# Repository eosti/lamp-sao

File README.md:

# Lamp SAOs
A few lamp-related SAOs. 

## HPL Lamp SAO

### Build Notes
- Requires 2x 28mm LED filaments and 2x ??mm 0.8mm dia. "jewelery wire" (tinned copper? not sure)
- Bend the longer wire so that it has a ?-shape on top and a very slight jog to the left (front view) towards the bottom
- Using the smaller jig, solder the non-hole side to the ? shape to form the filament assembly
- Using the larger jig, solder to SAO
- Bend another wire that makes a complicated shape. It's hard to explain in words. Solder this to the SAO. 
- Solder the other end to the bottom of the filaments. MAKE SURE THE TWO WIRES AREN'T BRIDGED. 

### Changelog
**V0 -> V1**
- Flip NPN footprints to be correct
- Reduce R5 to 30ohm
- Thermal relief on GND wire pad
- Replace 2N3904 with dual 3904 package
- Be a bit less hacky with the external PWM buffer
- Replace 555 diodes with a dual diode package

## C9 Lamp SAO
A SAO based on a C9 holiday lamp. 

### Build Notes
- Requires 2x 28mm LED filaments and 1x 28mm 0.8mm dia. "jewelery wire" (tinned copper? not sure)
- Using the C9 jig, solder the two filaments and the wire to the PCB
    - The hole-side of the filament should be on the top of the SAO, and the side of the filament that has a white rectangle peeking through should be on the back side of the SAO
    - For white filaments, the side that looks more orange should be facing the front of the SAO
- Remove from jig, and then solder the tops of the filaments to the wire on the front side
    - May need to bend the wire forward a bit to be coplanar with the filament leads
- Trim top of wire

### Changelog
- Schematics the same as HPL v1

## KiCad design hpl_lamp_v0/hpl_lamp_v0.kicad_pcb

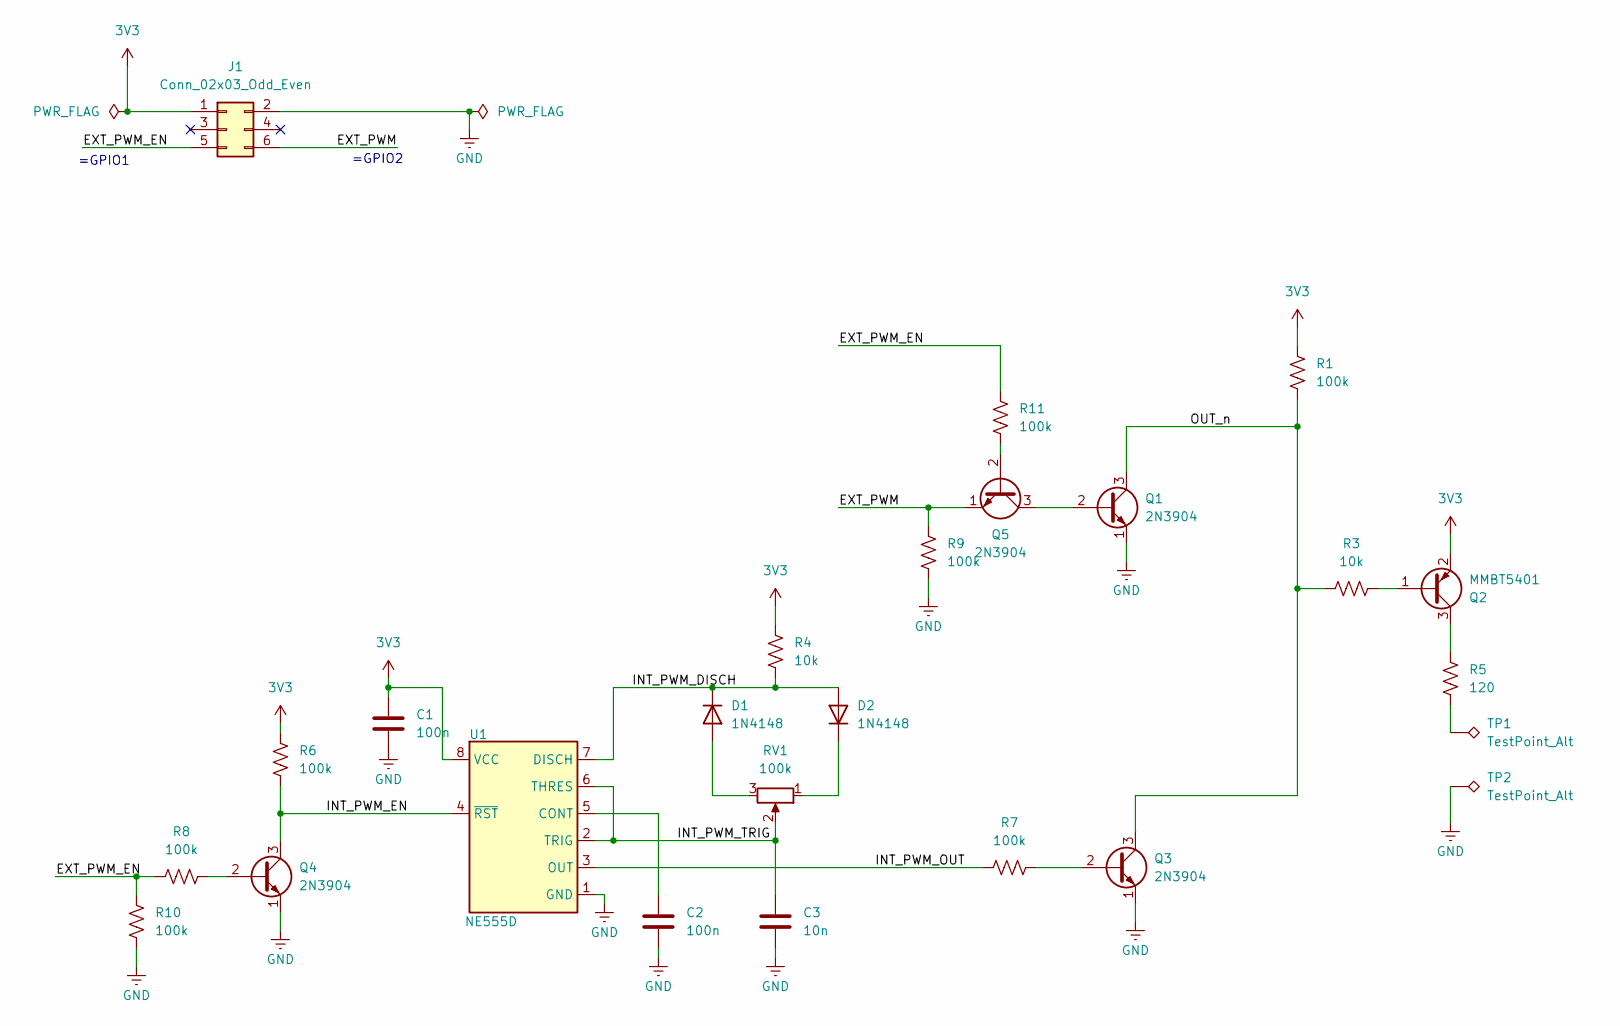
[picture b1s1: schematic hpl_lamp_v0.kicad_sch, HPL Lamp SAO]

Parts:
C1, C2: 100n; C_0603_1608Metric; LCSC C14663
C3: 10n; C_0603_1608Metric; LCSC C57112
D1, D2: 1N4148; D_SOD-323; LCSC C2128
J1: Conn_02x03_Odd_Even; IDC-Header_2x03_P2.54mm_Vertical
Q1, Q3, Q4, Q5: 2N3904; SOT-23; LCSC C20526
Q2: MMBT5401; SOT-23; LCSC C8326
R1, R6, R7, R8, R9, R10, R11: 100k; R_0603_1608Metric; LCSC C25803
R3, R4: 10k; R_0603_1608Metric; LCSC C25804
R5: 120; R_0805_2012Metric; LCSC C17437
RV1: 100k; Potentiometer_Bourns_TC33X_Vertical; LCSC C48997895
TP1, TP2: TestPoint_Alt; filament_connection
U1: NE555D; SOIC-8_3.9x4.9mm_P1.27mm; LCSC C7593

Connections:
3V3: C1.1, J1.1, Q2.2 (E), R1.1, R4.1, R6.1, U1.8 (VCC)
/EXT_PWM: J1.6, Q5.1 (E), R9.1; also elsewhere on the board
/EXT_PWM_EN: J1.5, R8.2, R10.1, R11.1
/INT_PWM_DISCH: D1.1 (K), D2.2 (A), R4.2, U1.7 (DISCH)
/INT_PWM_EN: Q4.3 (C), R6.2, U1.4 (~RST)
/INT_PWM_OUT: R7.2, U1.3 (OUT)
/INT_PWM_TRIG: C3.1, RV1.2, U1.2 (TRIG), U1.6 (THRES)
/OUT_n: Q1.3 (C), Q3.3 (C), R1.2, R3.2
GND: C1.2, C2.2, C3.2, J1.2, Q1.1 (E), Q3.1 (E), Q4.1 (E), R9.2, R10.2, TP2.1 (1_1), U1.1 (GND)
unnamed: D1.2 (A), RV1.3
unnamed: D2.1 (K), RV1.1
unnamed 11: Q1.2 (B), Q5.3 (C); also elsewhere on the board
unnamed: Q2.1 (B), R3.1
unnamed: Q2.3 (C), R5.1
unnamed: Q3.2 (B), R7.1
unnamed: Q4.2 (B), R8.1
unnamed: Q5.2 (B), R11.2
unnamed: R5.2, TP1.1 (1_1)
unnamed: C2.1, U1.5 (CONT)

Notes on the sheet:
=GPIO2
=GPIO1

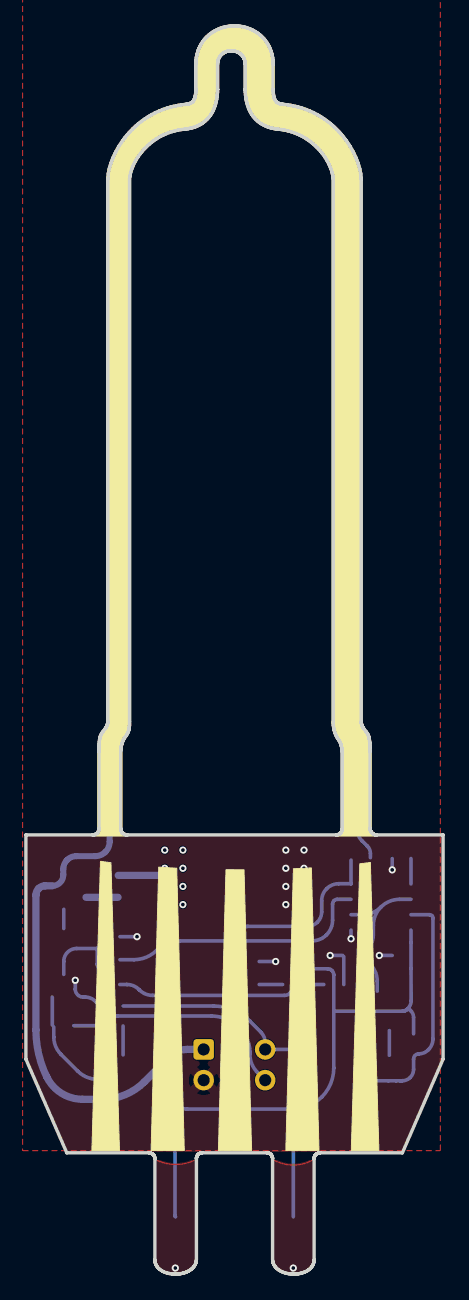
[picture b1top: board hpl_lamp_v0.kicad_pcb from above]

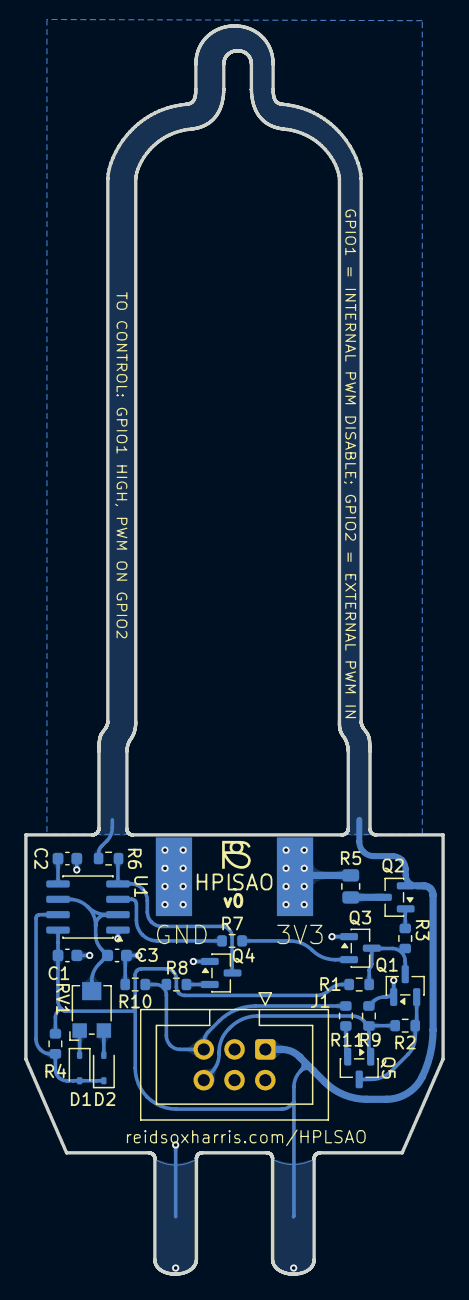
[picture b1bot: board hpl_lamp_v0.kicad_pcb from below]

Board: 2 copper layers, 34.5 x 103.1 mm, 26 parts (26 on the bottom side), 19 nets.

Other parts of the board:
R2: 10k; R_0603_1608Metric

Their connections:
/EXT_PWM: R2.2; also elsewhere on the board
unnamed 11: R2.1; also elsewhere on the board

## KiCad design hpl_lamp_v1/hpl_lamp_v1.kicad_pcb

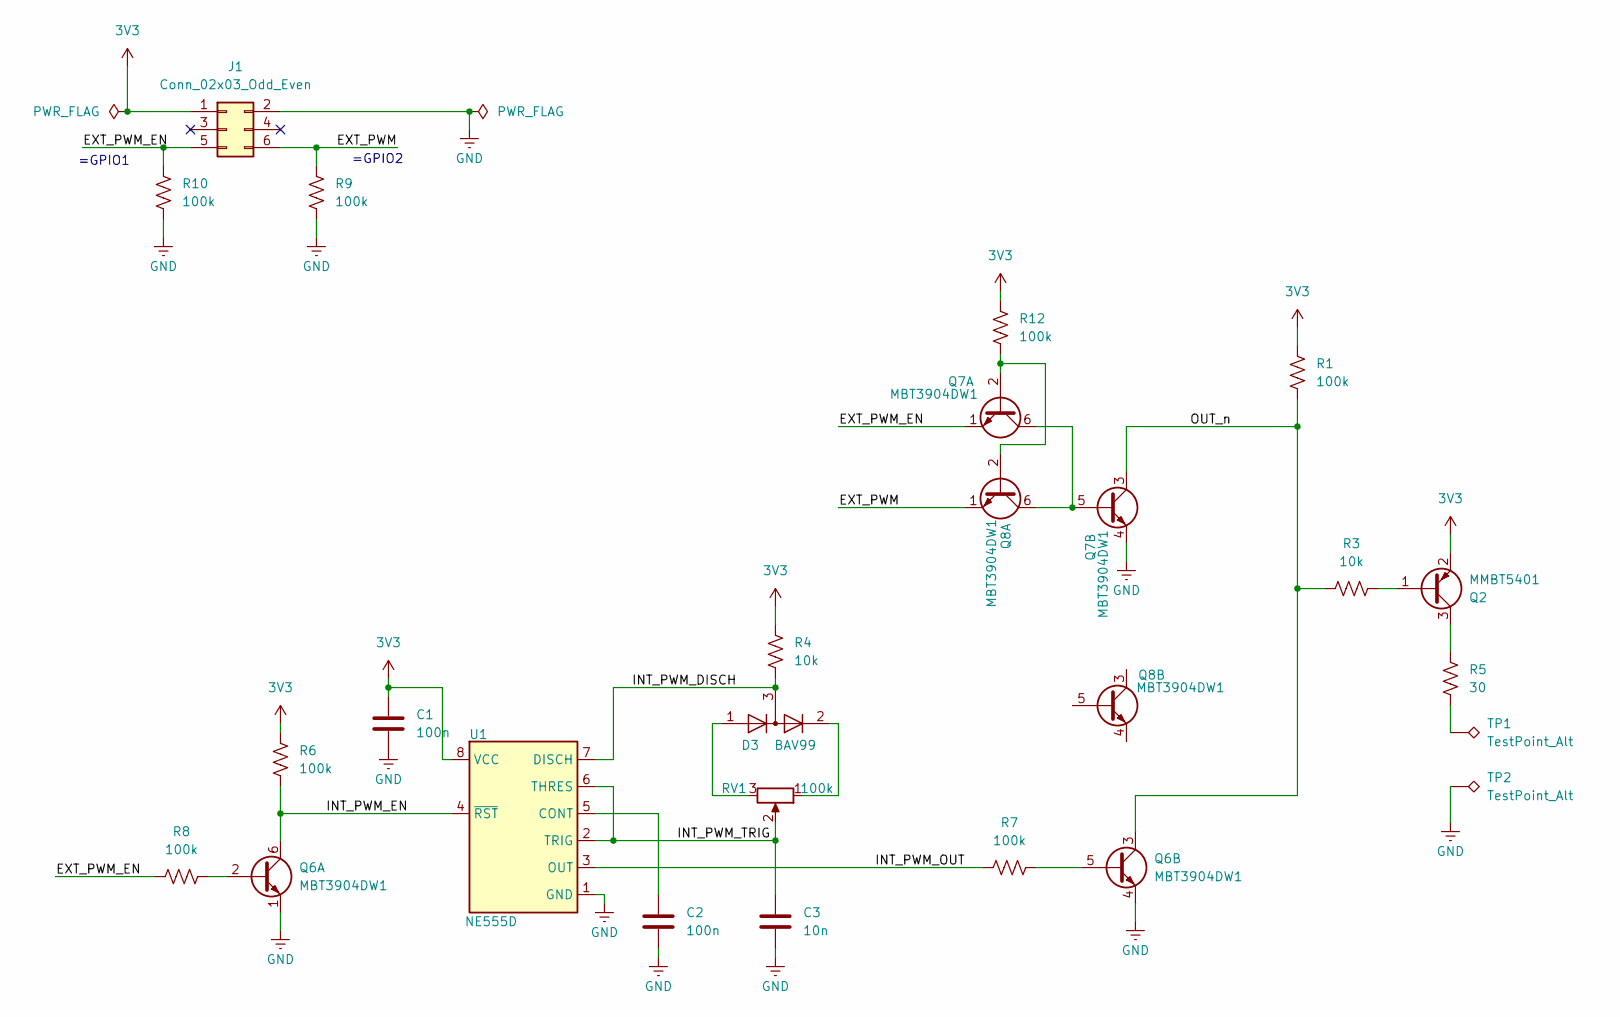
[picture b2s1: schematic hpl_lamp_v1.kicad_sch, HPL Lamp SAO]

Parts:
C1, C2: 100n; C_0603_1608Metric; LCSC C14663
C3: 10n; C_0603_1608Metric; LCSC C57112
D3: BAV99; SOT-23
J1: Conn_02x03_Odd_Even; PinHeader_2x03_P2.54mm_Vertical_SMD
Q2: MMBT5401; SOT-23; LCSC C8326
Q6, Q7, Q8: MBT3904DW1; SOT-363_SC-70-6
R1, R6, R7, R8, R9, R10, R12: 100k; R_0603_1608Metric; LCSC C25803
R3, R4: 10k; R_0603_1608Metric; LCSC C25804
R5: 30; R_0805_2012Metric; LCSC C17437
RV1: 100k; Potentiometer_Bourns_TC33X_Vertical; LCSC C48997895
TP1, TP2: TestPoint_Alt; filament_connection
U1: NE555D; SOIC-8_3.9x4.9mm_P1.27mm; LCSC C7593

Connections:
3V3: C1.1, J1.1, Q2.2 (E), R1.1, R4.1, R6.1, R12.1, U1.8 (VCC)
/EXT_PWM: J1.6, Q8.1 (E1), R9.1
/EXT_PWM_EN: J1.5, Q7.1 (E1), R8.2, R10.1
/INT_PWM_DISCH: D3.3 (K), R4.2, U1.7 (DISCH)
/INT_PWM_EN: Q6.6 (C1), R6.2, U1.4 (~RST)
/INT_PWM_OUT: R7.2, U1.3 (OUT)
/INT_PWM_TRIG: C3.1, RV1.2, U1.2 (TRIG), U1.6 (THRES)
/OUT_n: Q6.3 (C2), Q7.3 (C2), R1.2, R3.2
GND: C1.2, C2.2, C3.2, J1.2, Q6.1 (E1), Q6.4 (E2), Q7.4 (E2), R9.2, R10.2, TP2.1 (1_1), U1.1 (GND)
unnamed: D3.2 (A), RV1.1
unnamed: D3.1 (K), RV1.3
unnamed: Q2.1 (B), R3.1
unnamed: Q2.3 (C), R5.1
unnamed: Q6.2 (B1), R8.1
unnamed: Q6.5 (B2), R7.1
unnamed: Q7.2 (B1), Q8.2 (B1), R12.2
unnamed: Q7.5 (B2), Q7.6 (C1), Q8.6 (C1)
unnamed: R5.2, TP1.1 (1_1)
unnamed: C2.1, U1.5 (CONT)

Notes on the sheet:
=GPIO2
=GPIO1

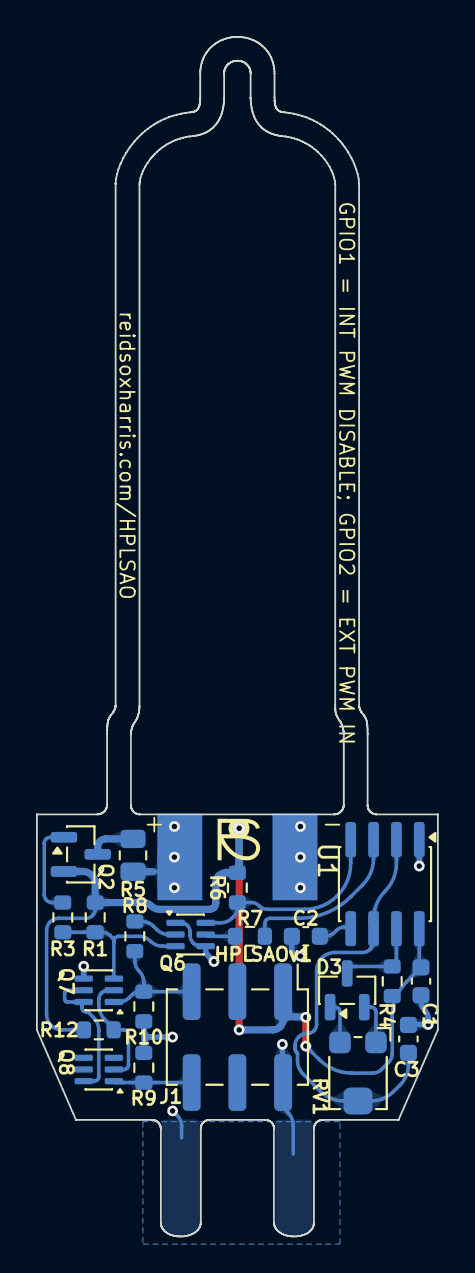
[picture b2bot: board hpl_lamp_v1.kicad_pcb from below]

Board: 2 copper layers, 22.3 x 66.6 mm, 23 parts (23 on the bottom side), 19 nets.
